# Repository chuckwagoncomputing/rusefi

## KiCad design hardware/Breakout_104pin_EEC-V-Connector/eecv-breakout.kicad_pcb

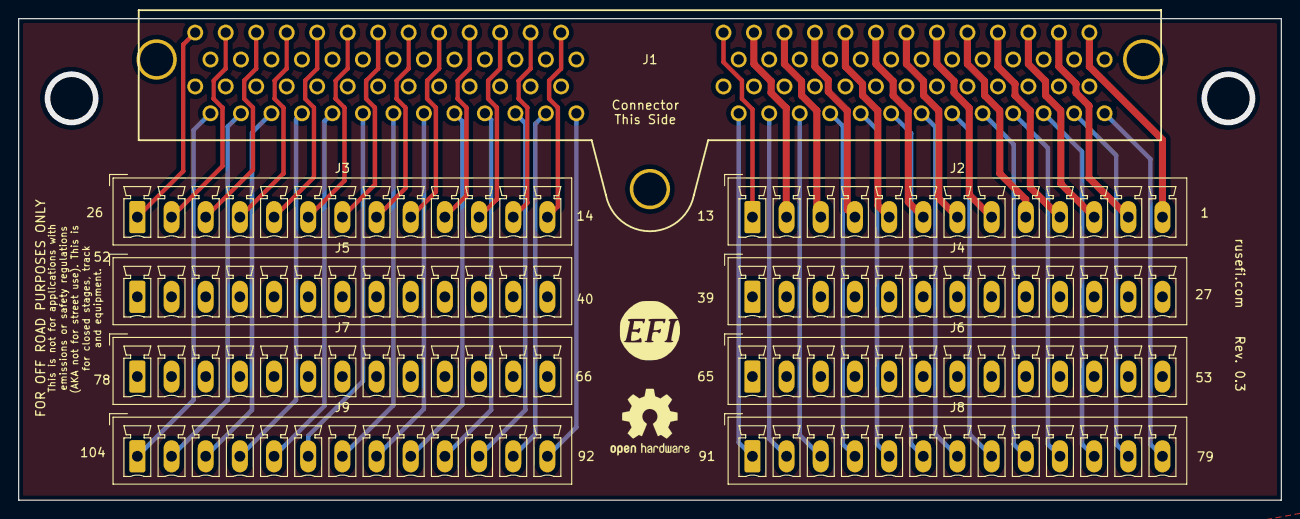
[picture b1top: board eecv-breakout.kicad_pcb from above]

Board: 4 copper layers, 140.8 x 53.7 mm, 11 parts (0 on the bottom side), 104 nets.

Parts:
G?: LOGO
G?#2: Disclaimer; Off_Road_Disclaimer
J1: EEC-V; eecv
J2, J3, J4, J5, J6, J7, J8, J9: Conn_01x13; PhoenixContact_MCV_1,5_13-G-3.81_1x13_P3.81mm_Vertical

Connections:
unnamed: J1.1, J2.13
unnamed: J1.2, J2.12
unnamed: J1.3, J2.11
unnamed: J1.4, J2.10
unnamed: J1.5, J2.9
unnamed: J1.6, J2.8
unnamed: J1.7, J2.7
unnamed: J1.8, J2.6
unnamed: J1.9, J2.5
unnamed: J1.10, J2.4
unnamed: J1.11, J2.3
unnamed: J1.12, J2.2
unnamed: J1.13, J2.1
unnamed: J1.14, J3.13
unnamed: J1.15, J3.12
unnamed: J1.16, J3.11
unnamed: J1.17, J3.10
unnamed: J1.18, J3.9
unnamed: J1.19, J3.8
unnamed: J1.20, J3.7
unnamed: J1.21, J3.6
unnamed: J1.22, J3.5
unnamed: J1.23, J3.4
unnamed: J1.24, J3.3
unnamed: J1.25, J3.2
unnamed: J1.26, J3.1
unnamed: J1.27, J4.13
unnamed: J1.28, J4.12
unnamed: J1.29, J4.11
unnamed: J1.30, J4.10
unnamed: J1.31, J4.9
unnamed: J1.32, J4.8
unnamed: J1.33, J4.7
unnamed: J1.34, J4.6
unnamed: J1.35, J4.5
unnamed: J1.36, J4.4
unnamed: J1.37, J4.3
unnamed: J1.38, J4.2
unnamed: J1.39, J4.1
unnamed: J1.40, J5.13
unnamed: J1.41, J5.12
unnamed: J1.42, J5.11
unnamed: J1.43, J5.10
unnamed: J1.44, J5.9
unnamed: J1.45, J5.8
unnamed: J1.46, J5.7
unnamed: J1.47, J5.6
unnamed: J1.48, J5.5
unnamed: J1.49, J5.4
unnamed: J1.50, J5.3
unnamed: J1.51, J5.2
unnamed: J1.52, J5.1
unnamed: J1.53, J6.13
unnamed: J1.54, J6.12
unnamed: J1.55, J6.11
unnamed: J1.56, J6.10
unnamed: J1.57, J6.9
unnamed: J1.58, J6.8
unnamed: J1.59, J6.7
unnamed: J1.60, J6.6
unnamed: J1.61, J6.5
unnamed: J1.62, J6.4
unnamed: J1.63, J6.3
unnamed: J1.64, J6.2
unnamed: J1.65, J6.1
unnamed: J1.66, J7.13
unnamed: J1.67, J7.12
unnamed: J1.68, J7.11
unnamed: J1.69, J7.10
unnamed: J1.70, J7.9
unnamed: J1.71, J7.8
unnamed: J1.72, J7.7
unnamed: J1.73, J7.6
unnamed: J1.74, J7.5
unnamed: J1.75, J7.4
unnamed: J1.76, J7.3
unnamed: J1.77, J7.2
unnamed: J1.78, J7.1
unnamed: J1.79, J8.13
unnamed: J1.80, J8.12
unnamed: J1.81, J8.11
unnamed: J1.82, J8.10
unnamed: J1.83, J8.9
unnamed: J1.84, J8.8
unnamed: J1.85, J8.7
unnamed: J1.86, J8.6
unnamed: J1.87, J8.5
unnamed: J1.88, J8.4
unnamed: J1.89, J8.3
unnamed: J1.90, J8.2
unnamed: J1.91, J8.1
unnamed: J1.92, J9.13
unnamed: J1.93, J9.12
unnamed: J1.94, J9.11
unnamed: J1.95, J9.10
unnamed: J1.96, J9.9
unnamed: J1.97, J9.8
unnamed: J1.98, J9.7
unnamed: J1.99, J9.6
unnamed: J1.100, J9.5
unnamed: J1.101, J9.4
unnamed: J1.102, J9.3
unnamed: J1.103, J9.2
unnamed: J1.104, J9.1

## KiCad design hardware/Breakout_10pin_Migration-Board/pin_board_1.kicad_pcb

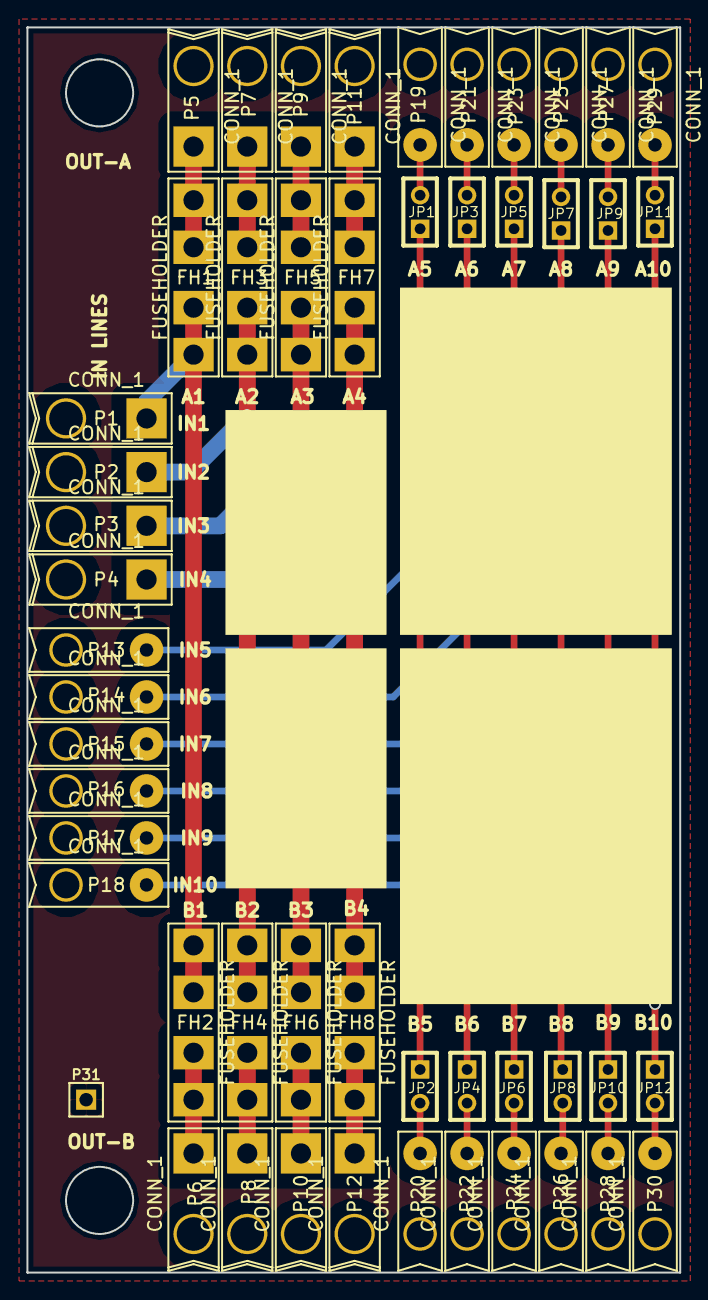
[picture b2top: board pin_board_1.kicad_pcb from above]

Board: 2 copper layers, 49.4 x 94.2 mm, 51 parts (0 on the bottom side), 30 nets.

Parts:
FH1, FH2, FH3, FH4, FH5, FH6, FH7, FH8: FUSEHOLDER
JP1, JP2, JP3, JP4, JP5, JP6, JP7, JP8, JP9, JP10, JP11, JP12: JUMPER; JUMPER-2
P1, P2, P3, P4, P5, P6, P7, P8, P9, P10, P11, P12: CONN_1; PIN_1_16AWG
P13, P14, P15, P16, P17, P18, P19, P20, P21, P22, P23, P24, P25, P26, P27, P28, P29, P30: CONN_1; PIN_1_20AWG
P31: CONN_1; PIN_ARRAY_1

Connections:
unnamed: JP8.2, P26.1
unnamed: JP7.2, P25.1
unnamed: JP7.1, JP8.1, P16.1
unnamed: JP3.2, P21.1
unnamed: JP4.2, P22.1
unnamed: JP3.1, JP4.1, P14.1
unnamed: JP5.1, JP6.1, P15.1
unnamed: JP6.2, P24.1
unnamed: JP5.2, P23.1
unnamed: JP11.2, P29.1
unnamed: JP12.2, P30.1
unnamed: JP11.1, JP12.1, P18.1
unnamed: JP10.2, P28.1
unnamed: JP9.2, P27.1
unnamed: JP9.1, JP10.1, P17.1
unnamed: JP1.2, P19.1
unnamed: JP2.2, P20.1
unnamed: FH3.1, FH4.1, P2.1
unnamed: FH4.2, P8.1
unnamed: FH3.2, P7.1
unnamed: FH1.1, FH2.1, P1.1
unnamed: FH2.2, P6.1
unnamed: FH1.2, P5.1
unnamed: JP1.1, JP2.1, P13.1
unnamed: FH7.1, FH8.1, P4.1
unnamed: FH8.2, P12.1
unnamed: FH7.2, P11.1
unnamed: FH5.1, FH6.1, P3.1
unnamed: FH6.2, P10.1
unnamed: FH5.2, P9.1

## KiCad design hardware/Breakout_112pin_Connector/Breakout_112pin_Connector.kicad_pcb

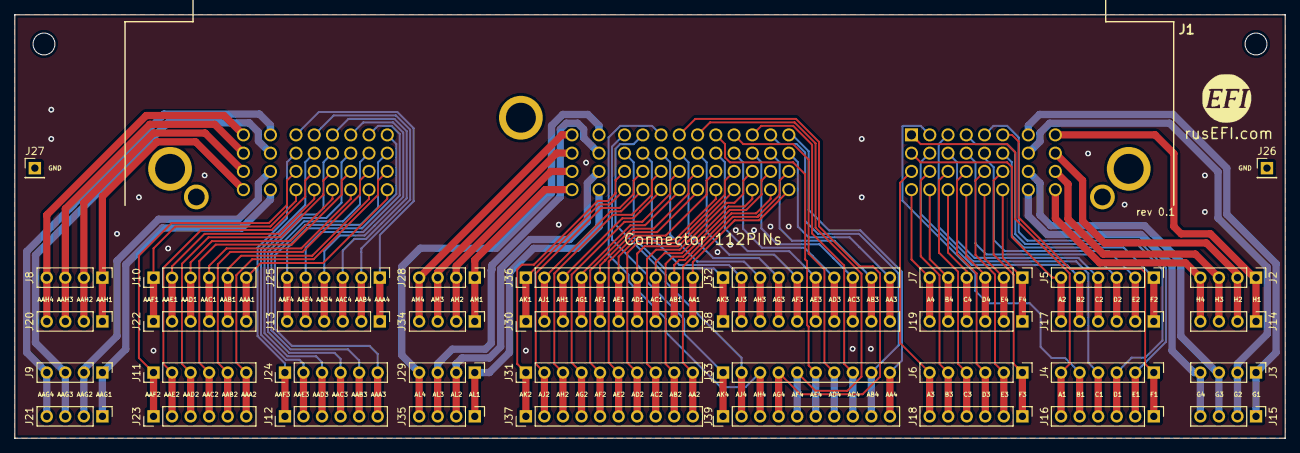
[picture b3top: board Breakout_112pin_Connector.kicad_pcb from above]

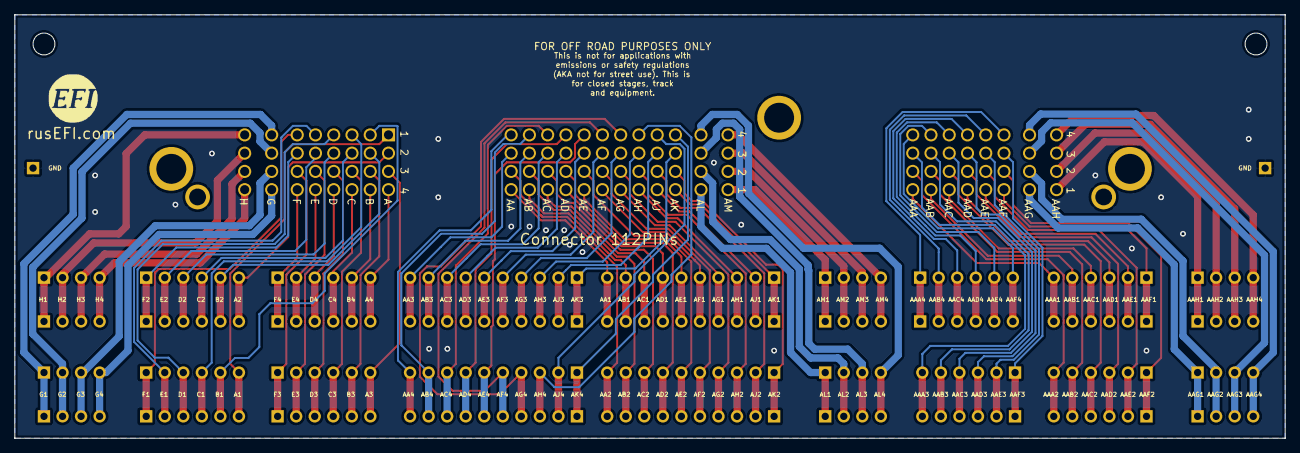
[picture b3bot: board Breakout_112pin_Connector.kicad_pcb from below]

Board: 2 copper layers, 174.0 x 58.0 mm, 42 parts (2 on the bottom side), 113 nets.

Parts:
G?: LOGO
G?#2: Disclaimer; Off_Road_Disclaimer
G?#3: LOGO
J1: 0643330100; 64333-0100_1
J2, J3, J8, J9, J14, J15, J20, J21, J28, J29, J34, J35: Conn_01x04; Pin_Header_Straight_1x04_Pitch2.54mm
J4, J5, J6, J7, J10, J11, J12, J13, J16, J17, J18, J19, J22, J23, J24, J25: Conn_01x06; Pin_Header_Straight_1x06_Pitch2.54mm
J26, J27: Conn_01x01; Pin_Header_Straight_1x01_Pitch2.54mm
J30, J31, J32, J33, J36, J37, J38, J39: Conn_01x10; Pin_Header_Straight_1x10_Pitch2.54mm

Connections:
Earth: J1.MH1, J1.MH2, J1.MH3, J1.MH4, J1.MH5, J26.1, J27.1
unnamed: J1.A1, J4.6, J16.6
unnamed: J1.A2, J5.6, J17.6
unnamed: J1.A3, J6.6, J18.6
unnamed: J1.A4, J7.6, J19.6
unnamed: J1.AA1, J30.10, J36.10
unnamed: J1.AA2, J31.10, J37.10
unnamed: J1.AA3, J32.10, J38.10
unnamed: J1.AA4, J33.10, J39.10
unnamed: J1.AAA1, J10.6, J22.6
unnamed: J1.AAA2, J11.6, J23.6
unnamed: J1.AAA3, J12.6, J24.6
unnamed: J1.AAA4, J13.6, J25.6
unnamed: J1.AAB1, J10.5, J22.5
unnamed: J1.AAB2, J11.5, J23.5
unnamed: J1.AAB3, J12.5, J24.5
unnamed: J1.AAB4, J13.5, J25.5
unnamed: J1.AAC1, J10.4, J22.4
unnamed: J1.AAC2, J11.4, J23.4
unnamed: J1.AAC3, J12.4, J24.4
unnamed: J1.AAC4, J13.4, J25.4
unnamed: J1.AAD1, J10.3, J22.3
unnamed: J1.AAD2, J11.3, J23.3
unnamed: J1.AAD3, J12.3, J24.3
unnamed: J1.AAD4, J13.3, J25.3
unnamed: J1.AAE1, J10.2, J22.2
unnamed: J1.AAE2, J11.2, J23.2
unnamed: J1.AAE3, J12.2, J24.2
unnamed: J1.AAE4, J13.2, J25.2
unnamed: J1.AAF1, J10.1, J22.1
unnamed: J1.AAF2, J11.1, J23.1
unnamed: J1.AAF3, J12.1, J24.1
unnamed: J1.AAF4, J13.1, J25.1
unnamed: J1.AAG1, J9.1, J21.1
unnamed: J1.AAG2, J9.2, J21.2
unnamed: J1.AAG3, J9.3, J21.3
unnamed: J1.AAG4, J9.4, J21.4
unnamed: J1.AAH1, J8.1, J20.1
unnamed: J1.AAH2, J8.2, J20.2
unnamed: J1.AAH3, J8.3, J20.3
unnamed: J1.AAH4, J8.4, J20.4
unnamed: J1.AB1, J30.9, J36.9
unnamed: J1.AB2, J31.9, J37.9
unnamed: J1.AB3, J32.9, J38.9
unnamed: J1.AB4, J33.9, J39.9
unnamed: J1.AC1, J30.8, J36.8
unnamed: J1.AC2, J31.8, J37.8
unnamed: J1.AC3, J32.8, J38.8
unnamed: J1.AC4, J33.8, J39.8
unnamed: J1.AD1, J30.7, J36.7
unnamed: J1.AD2, J31.7, J37.7
unnamed: J1.AD3, J32.7, J38.7
unnamed: J1.AD4, J33.7, J39.7
unnamed: J1.AE1, J30.6, J36.6
unnamed: J1.AE2, J31.6, J37.6
unnamed: J1.AE3, J32.6, J38.6
unnamed: J1.AE4, J33.6, J39.6
unnamed: J1.AF1, J30.5, J36.5
unnamed: J1.AF2, J31.5, J37.5
unnamed: J1.AF3, J32.5, J38.5
unnamed: J1.AF4, J33.5, J39.5
unnamed: J1.AG1, J30.4, J36.4
unnamed: J1.AG2, J31.4, J37.4
unnamed: J1.AG3, J32.4, J38.4
unnamed: J1.AG4, J33.4, J39.4
unnamed: J1.AH1, J30.3, J36.3
unnamed: J1.AH2, J31.3, J37.3
unnamed: J1.AH3, J32.3, J38.3
unnamed: J1.AH4, J33.3, J39.3
unnamed: J1.AJ1, J30.2, J36.2
unnamed: J1.AJ2, J31.2, J37.2
unnamed: J1.AJ3, J32.2, J38.2
unnamed: J1.AJ4, J33.2, J39.2
unnamed: J1.AK1, J30.1, J36.1
unnamed: J1.AK2, J31.1, J37.1
unnamed: J1.AK3, J32.1, J38.1
unnamed: J1.AK4, J33.1, J39.1
unnamed: J1.AL1, J29.1, J35.1
unnamed: J1.AL2, J29.2, J35.2
unnamed: J1.AL3, J29.3, J35.3
unnamed: J1.AL4, J29.4, J35.4
unnamed: J1.AM1, J28.1, J34.1
unnamed: J1.AM2, J28.2, J34.2
unnamed: J1.AM3, J28.3, J34.3
unnamed: J1.AM4, J28.4, J34.4
unnamed: J1.B1, J4.5, J16.5
unnamed: J1.B2, J5.5, J17.5
unnamed: J1.B3, J6.5, J18.5
unnamed: J1.B4, J7.5, J19.5
unnamed: J1.C1, J4.4, J16.4
unnamed: J1.C2, J5.4, J17.4
unnamed: J1.C3, J6.4, J18.4
unnamed: J1.C4, J7.4, J19.4
unnamed: J1.D1, J4.3, J16.3
unnamed: J1.D2, J5.3, J17.3
unnamed: J1.D3, J6.3, J18.3
unnamed: J1.D4, J7.3, J19.3
unnamed: J1.E1, J4.2, J16.2
unnamed: J1.E2, J5.2, J17.2
unnamed: J1.E3, J6.2, J18.2
unnamed: J1.E4, J7.2, J19.2
unnamed: J1.F1, J4.1, J16.1
unnamed: J1.F2, J5.1, J17.1
unnamed: J1.F3, J6.1, J18.1
unnamed: J1.F4, J7.1, J19.1
unnamed: J1.G1, J3.1, J15.1
unnamed: J1.G2, J3.2, J15.2
unnamed: J1.G3, J3.3, J15.3
unnamed: J1.G4, J3.4, J15.4
unnamed: J1.H1, J2.1, J14.1
unnamed: J1.H2, J2.2, J14.2
unnamed: J1.H3, J2.3, J14.3
unnamed: J1.H4, J2.4, J14.4

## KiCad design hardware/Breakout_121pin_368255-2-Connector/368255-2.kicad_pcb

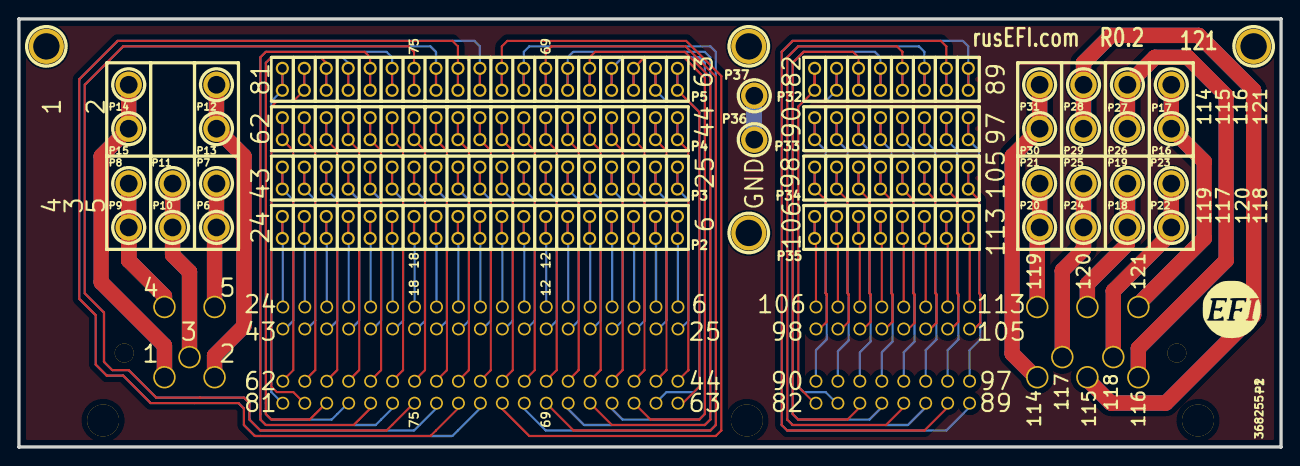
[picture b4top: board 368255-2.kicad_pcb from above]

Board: 2 copper layers, 146.1 x 49.5 mm, 43 parts (1 on the bottom side), 122 nets.

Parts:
1PIN, 1PIN#2, 1PIN#3, 1PIN#4: P***; 1pin
G?: LOGO
G?#2: LOGO; LOGO_F
P1: 368255-2
P2, P3, P4, P5: CONN_19; 19dpad
P6, P7, P8, P9, P10, P11, P12, P13, P14, P15, P16, P17, P18, P19, P20, P21, P22, P23, P24, P25, P26, P27, P28, P29, P30, P31, P36, P37: CONN_1; 1pin(m)
P32, P33, P34, P35: CONN_8; 8dpad

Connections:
GND: P36.1, P37.1
unnamed: P1.22, P2.17
unnamed: P1.34, P3.10
unnamed: P1.33, P3.9
unnamed: P1.32, P3.8
unnamed: P1.31, P3.7
unnamed: P1.30, P3.6
unnamed: P1.29, P3.5
unnamed: P1.28, P3.4
unnamed: P1.27, P3.3
unnamed: P1.26, P3.2
unnamed: P1.25, P3.1
unnamed: P1.24, P2.19
unnamed: P1.23, P2.18
unnamed: P1.35, P3.11
unnamed: P1.21, P2.16
unnamed: P1.20, P2.15
unnamed: P1.19, P2.14
unnamed: P1.18, P2.13
unnamed: P1.17, P2.12
unnamed: P1.16, P2.11
unnamed: P1.15, P2.10
unnamed: P1.14, P2.9
unnamed: P1.13, P2.8
unnamed: P1.12, P2.7
unnamed: P1.11, P2.6
unnamed: P1.10, P2.5
unnamed: P1.48, P4.5
unnamed: P1.60, P4.17
unnamed: P1.59, P4.16
unnamed: P1.58, P4.15
unnamed: P1.57, P4.14
unnamed: P1.56, P4.13
unnamed: P1.55, P4.12
unnamed: P1.54, P4.11
unnamed: P1.53, P4.10
unnamed: P1.52, P4.9
unnamed: P1.51, P4.8
unnamed: P1.50, P4.7
unnamed: P1.49, P4.6
unnamed: P1.9, P2.4
unnamed: P1.47, P4.4
unnamed: P1.46, P4.3
unnamed: P1.45, P4.2
unnamed: P1.44, P4.1
unnamed: P1.43, P3.19
unnamed: P1.42, P3.18
unnamed: P1.41, P3.17
unnamed: P1.40, P3.16
unnamed: P1.39, P3.15
unnamed: P1.38, P3.14
unnamed: P1.37, P3.13
unnamed: P1.36, P3.12
unnamed: P1.94, P33.5
unnamed: P1.106, P35.1
unnamed: P1.105, P34.8
unnamed: P1.104, P34.7
unnamed: P1.103, P34.6
unnamed: P1.102, P34.5
unnamed: P1.101, P34.4
unnamed: P1.100, P34.3
unnamed: P1.99, P34.2
unnamed: P1.98, P34.1
unnamed: P1.97, P33.8
unnamed: P1.96, P33.7
unnamed: P1.95, P33.6
unnamed: P1.107, P35.2
unnamed: P1.93, P33.4
unnamed: P1.92, P33.3
unnamed: P1.91, P33.2
unnamed: P1.90, P33.1
unnamed: P1.89, P32.8
unnamed: P1.88, P32.7
unnamed: P1.87, P32.6
unnamed: P1.86, P32.5
unnamed: P1.85, P32.4
unnamed: P1.84, P32.3
unnamed: P1.83, P32.2
unnamed: P1.82, P32.1
unnamed: P1.117, P24.1, P25.1
unnamed: P1.8, P2.3
unnamed: P1.7, P2.2
unnamed: P1.6, P2.1
unnamed: P1.120, P18.1, P19.1
unnamed: P1.118, P22.1, P23.1
unnamed: P1.61, P4.18
unnamed: P1.116, P26.1, P27.1
unnamed: P1.115, P28.1, P29.1
unnamed: P1.114, P30.1, P31.1
unnamed: P1.113, P35.8
unnamed: P1.112, P35.7
unnamed: P1.111, P35.6
unnamed: P1.110, P35.5
unnamed: P1.109, P35.4
unnamed: P1.108, P35.3
unnamed: P1.121, P16.1, P17.1
unnamed: P1.119, P20.1, P21.1
unnamed: P1.74, P5.12
unnamed: P1.81, P5.19
unnamed: P1.80, P5.18
unnamed: P1.79, P5.17
unnamed: P1.78, P5.16
unnamed: P1.77, P5.15
unnamed: P1.76, P5.14
unnamed: P1.75, P5.13
unnamed: P1.73, P5.11
unnamed: P1.72, P5.10
unnamed: P1.71, P5.9
unnamed: P1.70, P5.8
unnamed: P1.69, P5.7
unnamed: P1.68, P5.6
unnamed: P1.67, P5.5
unnamed: P1.66, P5.4
unnamed: P1.65, P5.3
unnamed: P1.64, P5.2
unnamed: P1.63, P5.1
unnamed: P1.62, P4.19
unnamed: P1.5, P6.1, P7.1
unnamed: P1.4, P8.1, P9.1
unnamed: P1.3, P10.1, P11.1
unnamed: P1.2, P12.1, P13.1
unnamed: P1.1, P14.1, P15.1

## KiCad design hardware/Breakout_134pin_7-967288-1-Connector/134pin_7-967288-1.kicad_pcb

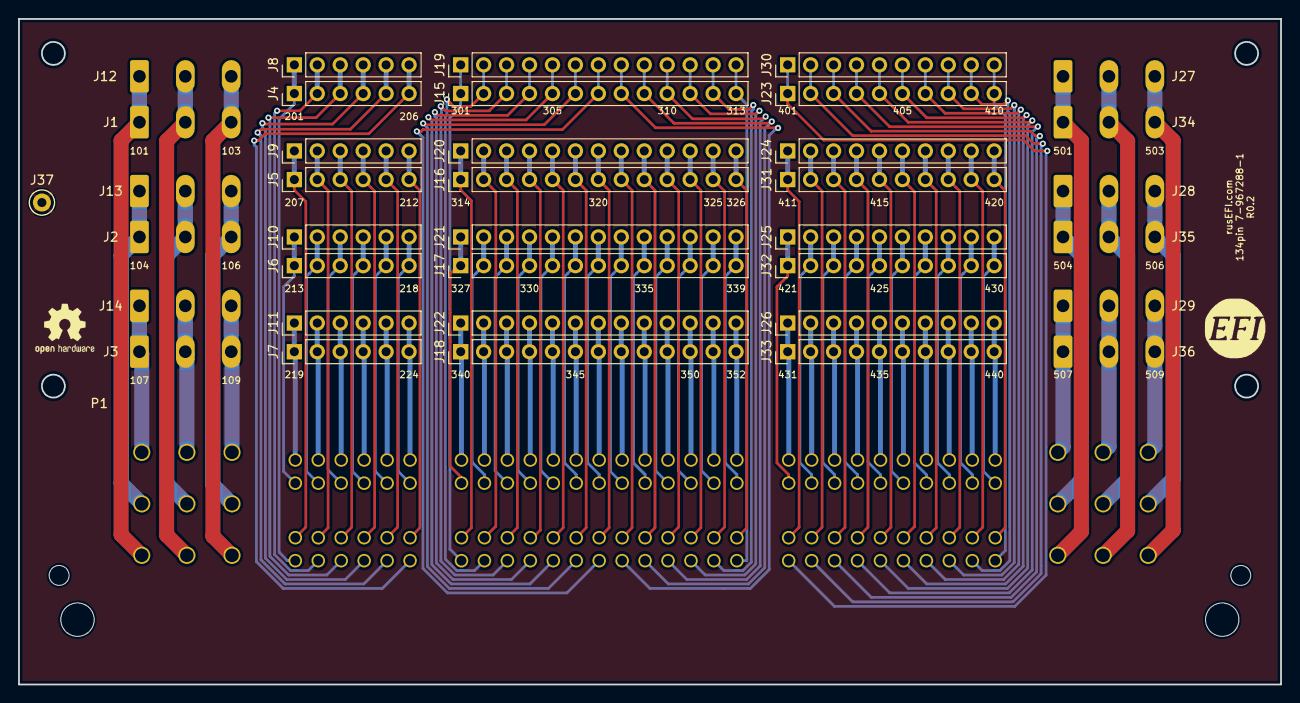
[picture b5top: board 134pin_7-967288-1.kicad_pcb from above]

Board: 2 copper layers, 139.7 x 73.7 mm, 40 parts (0 on the bottom side), 134 nets.

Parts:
J1, J2, J3, J12, J13, J14, J27, J28, J29, J34, J35, J36: Conn_01x03; PhoenixContact_MSTBA_2,5_3-G-5,08_1x03_P5.08mm_Horizontal
J4, J5, J6, J7, J8, J9, J10, J11: Conn_01x06; PinHeader_1x06_P2.54mm_Vertical
J15, J16, J17, J18, J19, J20, J21, J22: Conn_01x13; PinHeader_1x13_P2.54mm_Vertical
J23, J24, J25, J26, J30, J31, J32, J33: Conn_01x10; PinHeader_1x10_P2.54mm_Vertical
J37: Conn_01x01; TestPoint_Keystone_5000-5004_Miniature
LOGO1: DNP; LOGO
LOGO2: DNP; OSHW-Logo2_7.3x6mm_SilkScreen
P1: 134pin_7-967288-1_KC5; 7-967288-1_134-pin-connector

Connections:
/101: J1.1, J12.1, P1.101
/103: J1.3, J12.3, P1.103
/104: J2.1, J13.1, P1.104
/106: J2.3, J13.3, P1.106
/107: J3.1, J14.1, P1.107
/109: J3.3, J14.3, P1.109
/201: J4.1, J8.1, P1.201
/206: J4.6, J8.6, P1.206
/207: J5.1, J9.1, P1.207
/212: J5.6, J9.6, P1.212
/213: J6.1, J10.1, P1.213
/218: J6.6, J10.6, P1.218
/219: J7.1, J11.1, P1.219
/224: J7.6, J11.6, P1.224
/301: J15.1, J19.1, P1.301
/305: J15.5, J19.5, P1.305
/310: J15.10, J19.10, P1.310
/313: J15.13, J19.13, P1.313
/314: J16.1, J20.1, P1.314
/315: J16.2, J20.2, P1.315
/320: J16.7, J20.7, P1.320
/325: J16.12, J20.12, P1.325
/326: J16.13, J20.13, P1.326
/327: J17.1, J21.1, P1.327
/330: J17.4, J21.4, P1.330
/335: J17.9, J21.9, P1.335
/339: J17.13, J21.13, P1.339
/340: J18.1, J22.1, P1.340
/345: J18.6, J22.6, P1.345
/350: J18.11, J22.11, P1.350
/352: J18.13, J22.13, P1.352
/401: J23.1, J30.1, P1.401
/405: J23.5, J30.5, P1.405
/410: J23.10, J30.10, P1.410
/411: J24.1, J31.1, P1.411
/415: J24.5, J31.5, P1.415
/420: J24.10, J31.10, P1.420
/421: J25.1, J32.1, P1.421
/425: J25.5, J32.5, P1.425
/430: J25.10, J32.10, P1.430
/431: J26.1, J33.1, P1.431
/435: J26.5, J33.5, P1.435
/440: J26.10, J33.10, P1.440
/501: J27.1, J34.1, P1.501
/503: J27.3, J34.3, P1.503
/504: J28.1, J35.1, P1.504
/506: J28.3, J35.3, P1.506
/507: J29.1, J36.1, P1.507
/509: J29.3, J36.3, P1.509
unnamed: J1.2, J12.2, P1.102
unnamed: J4.2, J8.2, P1.202
unnamed: J4.3, J8.3, P1.203
unnamed: J4.4, J8.4, P1.204
unnamed: J4.5, J8.5, P1.205
unnamed: J5.2, J9.2, P1.208
unnamed: J5.3, J9.3, P1.209
unnamed: J5.4, J9.4, P1.210
unnamed: J5.5, J9.5, P1.211
unnamed: J6.2, J10.2, P1.214
unnamed: J6.3, J10.3, P1.215
unnamed: J6.4, J10.4, P1.216
unnamed: J6.5, J10.5, P1.217
unnamed: J7.2, J11.2, P1.220
unnamed: J7.3, J11.3, P1.221
unnamed: J7.4, J11.4, P1.222
unnamed: J7.5, J11.5, P1.223
unnamed: J2.2, J13.2, P1.105
unnamed: J3.2, J14.2, P1.108
unnamed: J15.2, J19.2, P1.302
unnamed: J15.3, J19.3, P1.303
unnamed: J15.4, J19.4, P1.304
unnamed: J15.6, J19.6, P1.306
unnamed: J15.7, J19.7, P1.307
unnamed: J15.8, J19.8, P1.308
unnamed: J15.9, J19.9, P1.309
unnamed: J15.11, J19.11, P1.311
unnamed: J15.12, J19.12, P1.312
unnamed: J16.3, J20.3, P1.316
unnamed: J16.4, J20.4, P1.317
unnamed: J16.5, J20.5, P1.318
unnamed: J16.6, J20.6, P1.319
unnamed: J16.8, J20.8, P1.321
unnamed: J16.9, J20.9, P1.322
unnamed: J16.10, J20.10, P1.323
unnamed: J16.11, J20.11, P1.324
unnamed: J17.2, J21.2, P1.328
unnamed: J17.3, J21.3, P1.329
unnamed: J17.5, J21.5, P1.331
unnamed: J17.6, J21.6, P1.332
unnamed: J17.7, J21.7, P1.333
unnamed: J17.8, J21.8, P1.334
unnamed: J17.10, J21.10, P1.336
unnamed: J17.11, J21.11, P1.337
unnamed: J17.12, J21.12, P1.338
unnamed: J18.2, J22.2, P1.341
unnamed: J18.3, J22.3, P1.342
unnamed: J18.4, J22.4, P1.343
unnamed: J18.5, J22.5, P1.344
unnamed: J18.7, J22.7, P1.346
unnamed: J18.8, J22.8, P1.347
unnamed: J18.9, J22.9, P1.348
unnamed: J18.10, J22.10, P1.349
unnamed: J18.12, J22.12, P1.351
unnamed: J23.2, J30.2, P1.402
unnamed: J23.3, J30.3, P1.403
unnamed: J23.4, J30.4, P1.404
unnamed: J23.6, J30.6, P1.406
unnamed: J23.7, J30.7, P1.407
unnamed: J23.8, J30.8, P1.408
unnamed: J23.9, J30.9, P1.409
unnamed: J24.2, J31.2, P1.412
unnamed: J24.3, J31.3, P1.413
unnamed: J24.4, J31.4, P1.414
unnamed: J24.6, J31.6, P1.416
unnamed: J24.7, J31.7, P1.417
unnamed: J24.8, J31.8, P1.418
unnamed: J24.9, J31.9, P1.419
unnamed: J25.2, J32.2, P1.422
unnamed: J25.3, J32.3, P1.423
unnamed: J25.4, J32.4, P1.424
unnamed: J25.6, J32.6, P1.426
unnamed: J25.7, J32.7, P1.427
unnamed: J25.8, J32.8, P1.428
unnamed: J25.9, J32.9, P1.429
unnamed: J26.2, J33.2, P1.432
unnamed: J26.3, J33.3, P1.433
unnamed: J26.4, J33.4, P1.434
unnamed: J26.6, J33.6, P1.436
unnamed: J26.7, J33.7, P1.437
unnamed: J26.8, J33.8, P1.438
unnamed: J26.9, J33.9, P1.439
unnamed: J27.2, J34.2, P1.502
unnamed: J28.2, J35.2, P1.505
unnamed: J29.2, J36.2, P1.508

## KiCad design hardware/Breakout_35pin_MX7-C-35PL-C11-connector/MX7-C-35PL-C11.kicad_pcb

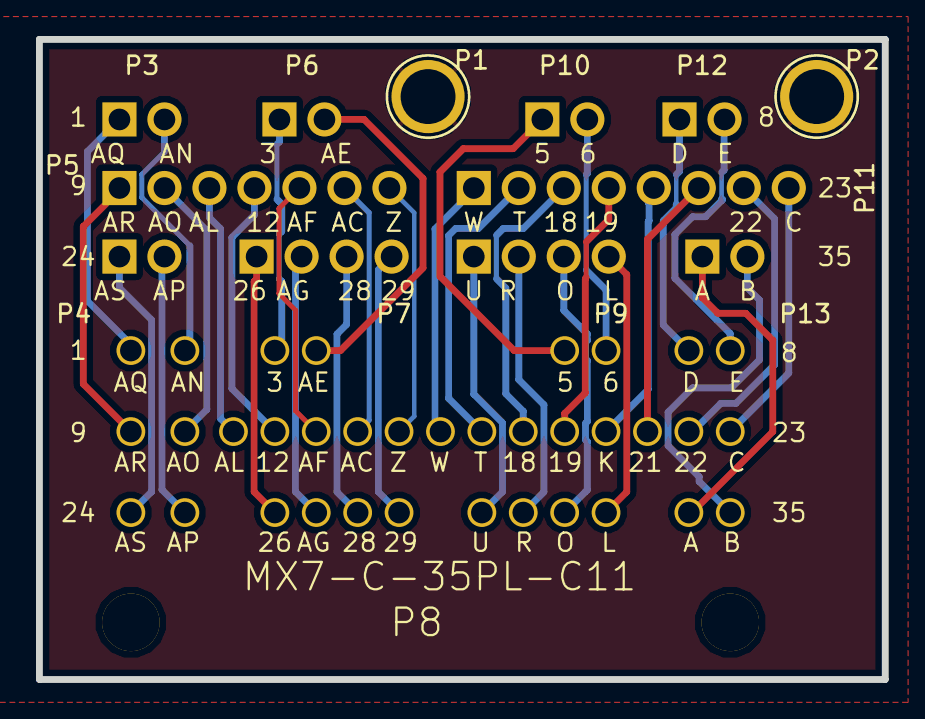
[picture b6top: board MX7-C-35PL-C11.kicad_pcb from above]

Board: 2 copper layers, 47.0 x 35.6 mm, 13 parts (0 on the bottom side), 36 nets.

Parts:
P1, P2: CONN_1; 1pin
P3, P4, P6, P10, P12, P13: CONN_01X02; Molex_NanoFit_1x02x2.50mm_Straight
P5: CONN_01X07; Molex_NanoFit_1x07x2.50mm_Straight
P7, P9: CONN_01X04; Molex_NanoFit_1x04x2.50mm_Straight
P8: MX7-C-35PL-C11
P11: CONN_01X08; Molex_NanoFit_1x08x2.50mm_Straight

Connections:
/3: P6.1, P8.3
/5: P8.5, P10.1
/6: P8.6, P10.2
/12: P5.4, P8.12
/18: P8.18, P11.3
/19: P8.19, P11.4
/21: P8.21, P11.6
/22: P8.22, P11.7
/26: P7.1, P8.26
/28: P7.3, P8.28
/29: P7.4, P8.29
/A: P8.34, P13.1
/AC: P5.6, P8.14
/AE: P6.2, P8.4
/AF: P5.5, P8.13
/AG: P7.2, P8.27
/AL: P5.3, P8.11
/AN: P3.2, P8.2
/AO: P5.2, P8.10
/AP: P4.2, P8.25
/AQ: P3.1, P8.1
/AR: P5.1, P8.9
/AS: P4.1, P8.24
/B: P8.35, P13.2
/C: P8.23, P11.8
/D: P8.7, P12.1
/F: P8.8, P12.2
/K: P8.20, P11.5
/L: P8.33, P9.4
/O: P8.32, P9.3
/R: P8.31, P9.2
/T: P8.17, P11.2
/U: P8.30, P9.1
/W: P8.16, P11.1
/Z: P5.7, P8.15
GND: P1.1, P2.1

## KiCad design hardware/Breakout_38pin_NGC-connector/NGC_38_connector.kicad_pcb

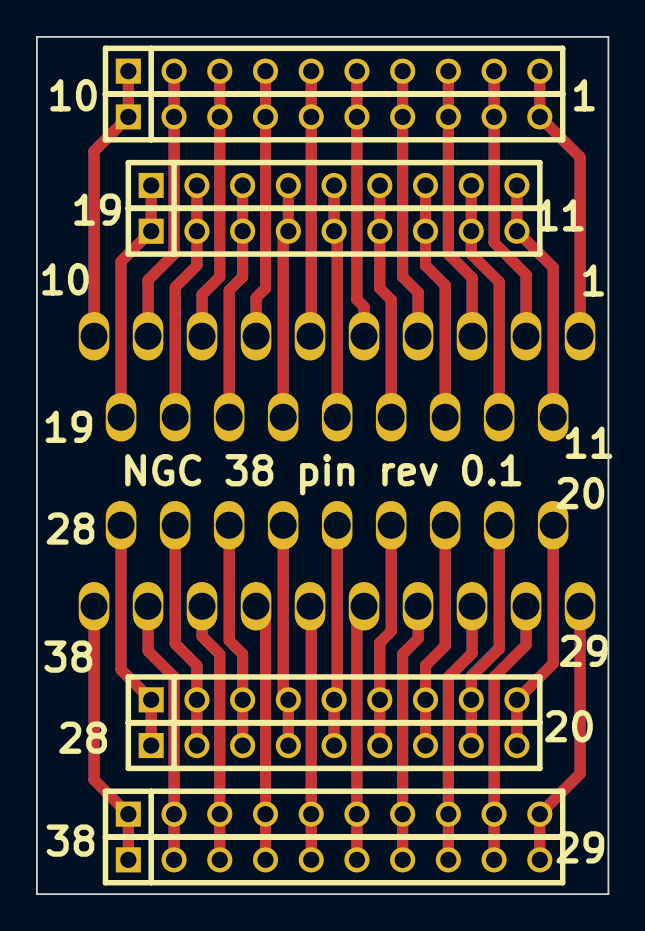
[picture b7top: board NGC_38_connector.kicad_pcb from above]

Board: 2 copper layers, 31.8 x 47.6 mm, 9 parts (0 on the bottom side), 38 nets.

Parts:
P1: DIL38; PCM_C1
P2, P4, P6, P9: CONN_10; SIL-10
P3, P5, P7, P8: CONN_9; SIL-9

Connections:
unnamed: P1.1, P2.1, P6.1
unnamed: P1.2, P2.2, P6.2
unnamed: P1.3, P2.3, P6.3
unnamed: P1.4, P2.4, P6.4
unnamed: P1.5, P2.5, P6.5
unnamed: P1.6, P2.6, P6.6
unnamed: P1.7, P2.7, P6.7
unnamed: P1.8, P2.8, P6.8
unnamed: P1.9, P2.9, P6.9
unnamed: P1.10, P2.10, P6.10
unnamed: P1.17, P3.7, P7.7
unnamed: P1.24, P5.5, P8.5
unnamed: P1.25, P5.6, P8.6
unnamed: P1.26, P5.7, P8.7
unnamed: P1.27, P5.8, P8.8
unnamed: P1.28, P5.9, P8.9
unnamed: P1.11, P3.1, P7.1
unnamed: P1.12, P3.2, P7.2
unnamed: P1.13, P3.3, P7.3
unnamed: P1.14, P3.4, P7.4
unnamed: P1.15, P3.5, P7.5
unnamed: P1.16, P3.6, P7.6
unnamed: P1.23, P5.4, P8.4
unnamed: P1.18, P3.8, P7.8
unnamed: P1.19, P3.9, P7.9
unnamed: P1.31, P4.3, P9.3
unnamed: P1.29, P4.1, P9.1
unnamed: P1.30, P4.2, P9.2
unnamed: P1.32, P4.4, P9.4
unnamed: P1.33, P4.5, P9.5
unnamed: P1.34, P4.6, P9.6
unnamed: P1.35, P4.7, P9.7
unnamed: P1.36, P4.8, P9.8
unnamed: P1.37, P4.9, P9.9
unnamed: P1.38, P4.10, P9.10
unnamed: P1.20, P5.1, P8.1
unnamed: P1.21, P5.2, P8.2
unnamed: P1.22, P5.3, P8.3
